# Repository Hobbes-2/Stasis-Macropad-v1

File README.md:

Stasis Macropad (v1)

My first PCB, as well as first project for forge. (Originally planned to be submitted to Stasis, hence the name)

A basic macropad with:
6 keys,
A rotary encoder switch,
A OLED display

This project is meant both as a useful tool for me to use (i might try using it for things like tetris or such) and a perfect learning oppertunity. I have never done hardware hackathons/projects before, so this is a really good chance for me to learn. I originally used the hackclub macropad tutorial, and then deviated from it to get to what i have now. (https://hackpad.hackclub.com/guide) 
The keys are arranged in a matrix, and the display and rotary encoder are wired in seprately (from the matrix). The microcontroller im using ([XIAO-SEEEDUINO](https://wiki.seeedstudio.com/Seeeduino-XIAO/)) has USB-C connection for power. The firmware is written in python with KMK. 

3D render of the pcb

Schematics and layout

Case

All together

Keys

BOM
|Name                        |Purpose                                                                   |Quantity|Total Cost (USD)|Link                                                                                 |Distributor    |
|----------------------------|--------------------------------------------------------------------------|--------|----------------|-------------------------------------------------------------------------------------|---------------|
|PCB                         |The actual pcb                                                            |1       |5.12            |                                                                                     |JLCPCB         |
|3d Printed Case & Keys      |The case and keys                                                         |1       |7               |                                                                                     |Printing Legion|
|Cherry MX Switch (MX1A-L1NN)|The keys of this macropad                                                 |6       |6               |https://www.mouser.com/ProductDetail/CHERRY/MX1A-L1NN?qs=F5EMLAvA7IDlALNAurZTXA%3D%3D|Mouser         |
|0.91" OLED Graphic 128x32   |The display of this macropad; im going to try to make it log recent inputs|1       |3.9            |https://www.amazon.com/gp/product/B079BN2J8V/ref=ox_sc_act_title_1?smid=A1N6DLY3NQK2VM&psc=1|Amazon  |
|SEEEDUINO XIAO              |The microcontroller of this macropad                                      |1       |5.4             |https://www.digikey.com/en/products/detail/seeed-technology-co-ltd/102010328/11506471|Digikey        |
|1N4148                      |Preventing ghosting in the keyboard matrix                                |6       |0.83             |https://www.digikey.com/en/products/detail/smc-diode-solutions/1N4148W/6022450                      |Digikey        |
|EC11E15244G1                |Changing volume                                                           |1       |4.63            |https://www.digikey.com/en/products/detail/alps-alpine/EC11E15244G1/21721550         |Digikey        |

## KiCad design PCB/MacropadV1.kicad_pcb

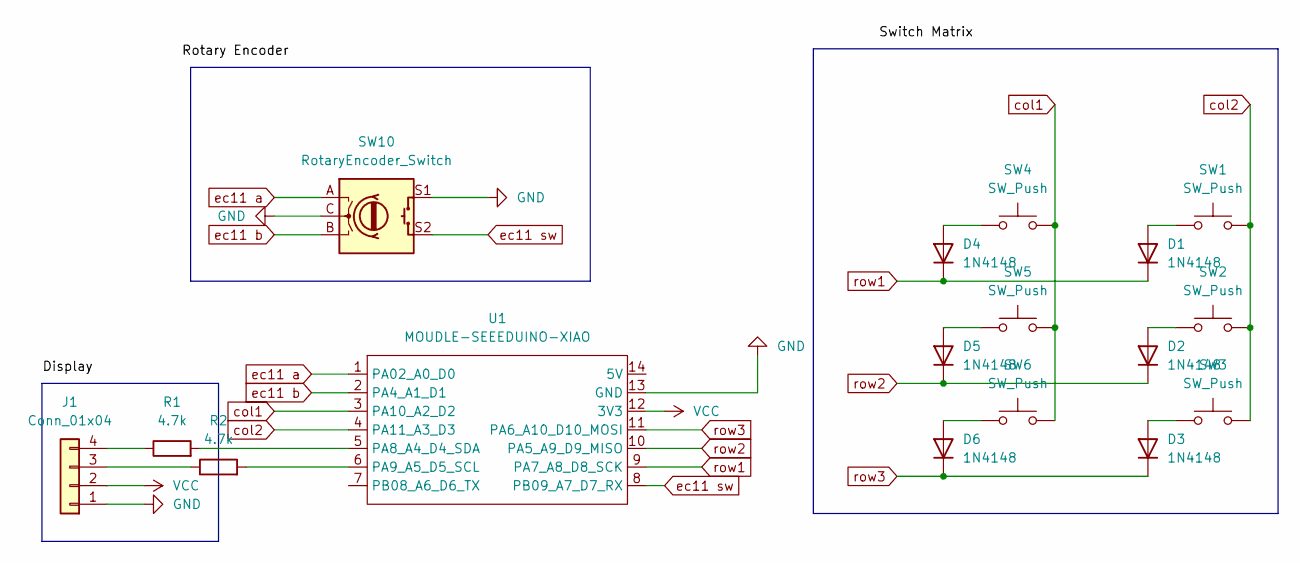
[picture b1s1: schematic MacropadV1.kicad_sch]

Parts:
D1, D2, D3, D4, D5, D6: 1N4148; D_SOD-123
J1: Conn_01x04; SSD1306-0.91-OLED-4pin-128x32
R1, R2: 4.7k; R_Axial_DIN0207_L6.3mm_D2.5mm_P10.16mm_Horizontal
SW1, SW2, SW3, SW4, SW5, SW6: SW_Push; SW_Cherry_MX_1.00u_PCB
SW10: RotaryEncoder_Switch; RotaryEncoder_Alps_EC11E-Switch_Vertical_H20mm
U1: MOUDLE-SEEEDUINO-XIAO; XIAO-Generic-Hybrid-14P-2.54-21X17.8MM

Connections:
GND: J1.1, SW10.C, SW10.S1, U1.13 (GND)
unnamed: D1.2 (A), SW1.1
unnamed: D2.2 (A), SW2.1
unnamed: D3.2 (A), SW3.1
unnamed: D4.2 (A), SW4.1
unnamed: D5.2 (A), SW5.1
unnamed: D6.2 (A), SW6.1
unnamed: J1.3, R2.1
unnamed: J1.4, R1.1
unnamed: R1.2, U1.5 (PA8_A4_D4_SDA)
unnamed: R2.2, U1.6 (PA9_A5_D5_SCL)
VCC: J1.2, U1.12 (3V3)
col1: SW4.2, SW5.2, SW6.2, U1.3 (PA10_A2_D2)
col2: SW1.2, SW2.2, SW3.2, U1.4 (PA11_A3_D3)
ec11 a: SW10.A, U1.1 (PA02_A0_D0)
ec11 b: SW10.B, U1.2 (PA4_A1_D1)
ec11 sw: SW10.S2, U1.8 (PB09_A7_D7_RX)
row1: D1.1 (K), D4.1 (K), U1.9 (PA7_A8_D8_SCK)
row2: D2.1 (K), D5.1 (K), U1.10 (PA5_A9_D9_MISO)
row3: D3.1 (K), D6.1 (K), U1.11 (PA6_A10_D10_MOSI)

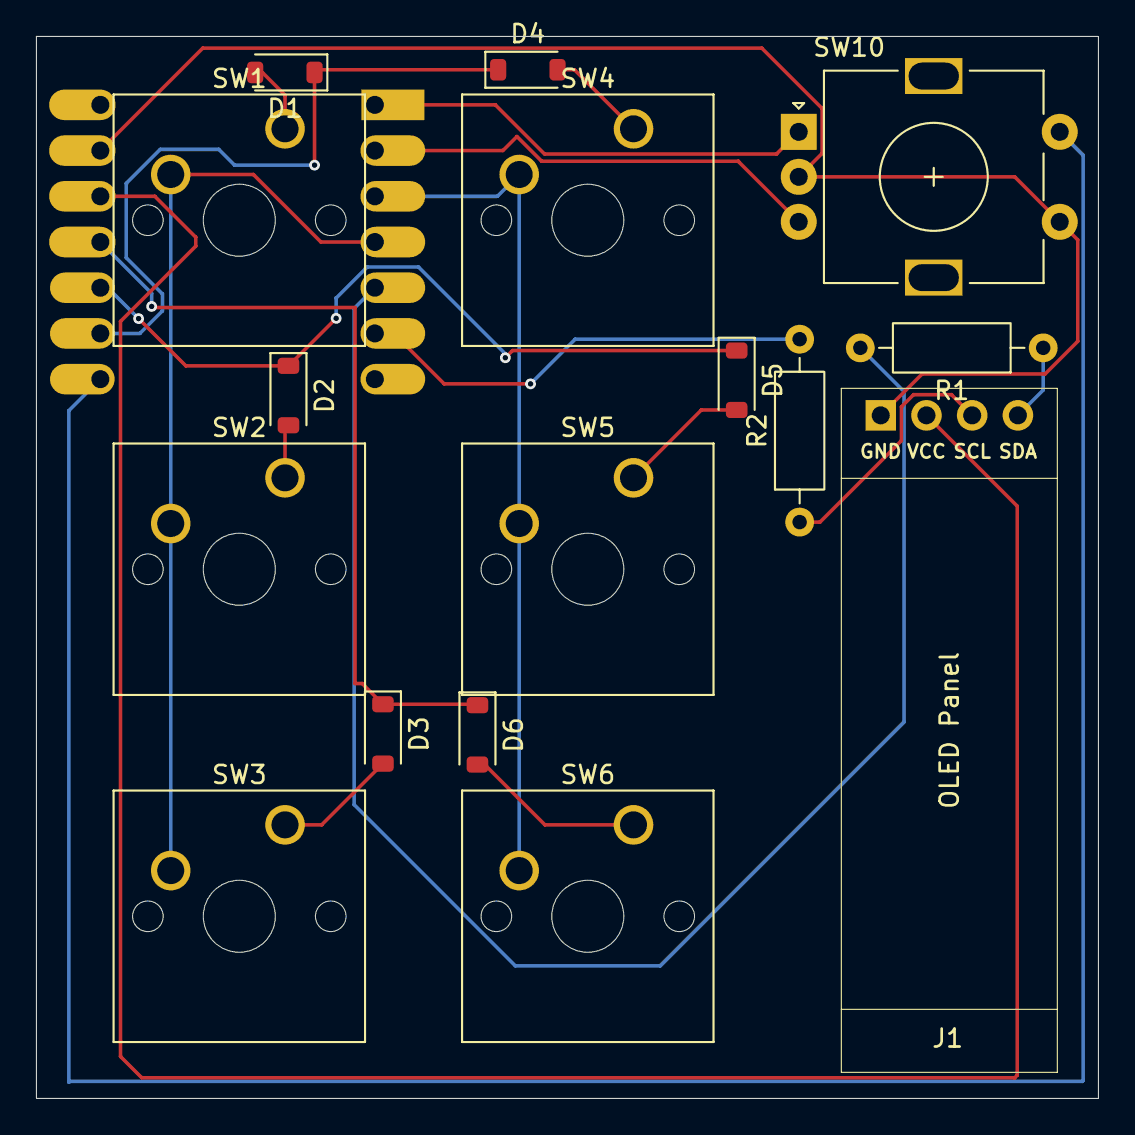
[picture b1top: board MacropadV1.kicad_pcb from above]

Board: 2 copper layers, 59.0 x 59.0 mm, 17 parts (1 on the bottom side), 20 nets.

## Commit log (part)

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2026-04-10 commiting for the first time
2026-04-11 Added readme
2026-04-23 added case 3d models and updated pcb
2026-04-23 dealing with git issues
2026-04-23 updated firmware
2026-04-24 updated firmware to include display. right now it should just display an image
2026-04-24 Update README.md to everything BUT the BOM
2026-04-25 just making sure i didnt forget anything
2026-04-26 added a silkscreen image and added gerber files
2026-04-26 making sure no files got left out
2026-04-26 Added BOM to README
2026-04-26 Screwed up the BOM, should be fixed now
2026-04-26 Updated CAD pictures in readme
2026-04-26 Was stupid and put the images in the wrong area but it SHOULD be right now
2026-05-03 Changed OLED link and updated details
2026-05-04 updated bom link
2026-05-18 updated case 3d model
2026-05-19 Update README.md with pcb render
2026-05-27 fixed schematic display error
2026-05-28 Add full cad screenshot to README
2026-05-29 Fixed schematic image
2026-06-14 added bom file
2026-06-14 added full 3d models
2026-06-15 Fixed diode link on bom
2026-06-15 Fixed pricing on bom (im lowk stupidddd)
2026-06-24 updated pcb price on bom
2026-06-24 Updated PCB price
